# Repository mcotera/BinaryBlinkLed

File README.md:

# BinaryBlinkLed

# Program used
Eclipse CDT
KiCad
LibreOffice

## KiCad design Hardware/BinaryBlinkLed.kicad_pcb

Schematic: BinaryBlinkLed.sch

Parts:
BT1: 3V; JG_BAT
C1: 100nF; C_0805
D1: Led_01; Led_1206
D2, D3: Led_02; Led_1206
IC1: ATTINY13A-SS; so-8
P2: ISCP6; Pin_Header_Straight_2x03
Q1, Q2, Q3: BC848; SOT-23
R1, R2, R4, R6: 10K; r_0805
R3, R5, R7: 82R; r_0805
SW1: Switch_SPDT_x2; push_lock_6mm

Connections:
+BATT: C1.1, IC1.8 (VCC), P2.2, R1.2, R3.2, R5.2, R7.2, SW1.6
/LED02: IC1.2 (PB3(CLKI/ADC3/PCINT3)), R2.2
/LED03: IC1.3 (PB4(ADC2/PCINT4)), R4.2
/MISO: IC1.6 (PB1(MISO/AIN1/OC0B/INT0/PCINT1)), P2.1
/MOSI: IC1.5 (PB0(MOSI/AIN0/OC0A/PCINT0)), P2.4, R6.2
/RST: IC1.1 (PB5(~RESET~/ADC0/PCINT5/dW)), P2.5, R1.1
/SCK: IC1.7 (PB2(SCK/ADC1/T0/PCINT2)), P2.3
GND: BT1.2, C1.2, IC1.4 (GND), P2.6, Q1.2 (E), Q2.2 (E), Q3.2 (E)
unnamed: BT1.1, SW1.5
unnamed: D1.1 (K), Q1.3 (C)
unnamed: D1.2 (A), R3.1
unnamed: D2.1 (K), Q2.3 (C)
unnamed: D2.2 (A), R5.1
unnamed: D3.1 (K), Q3.3 (C)
unnamed: D3.2 (A), R7.1
unnamed: Q1.1 (B), R2.1
unnamed: Q2.1 (B), R4.1
unnamed: Q3.1 (B), R6.1

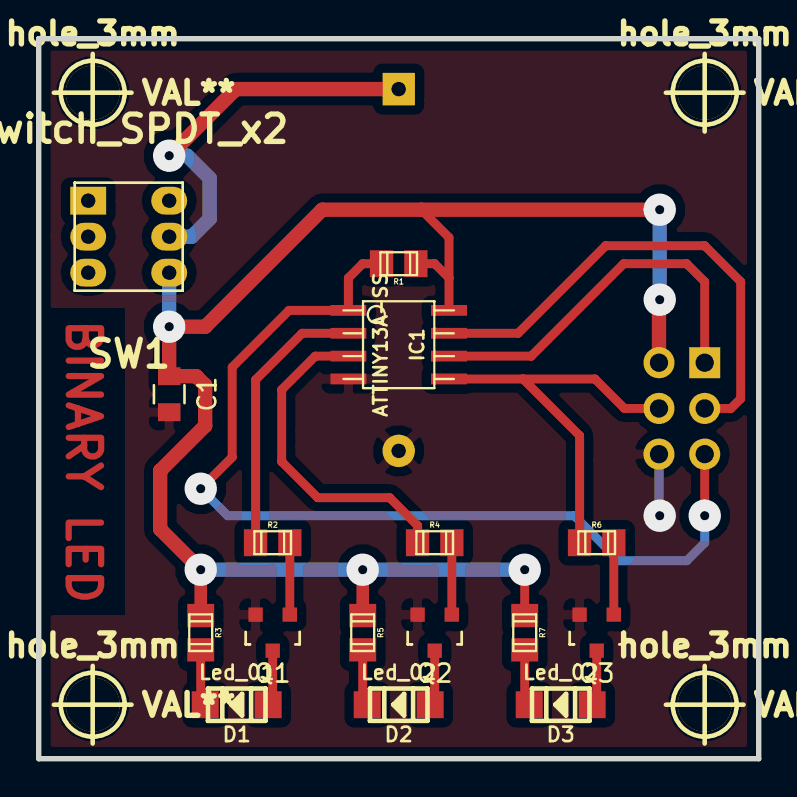
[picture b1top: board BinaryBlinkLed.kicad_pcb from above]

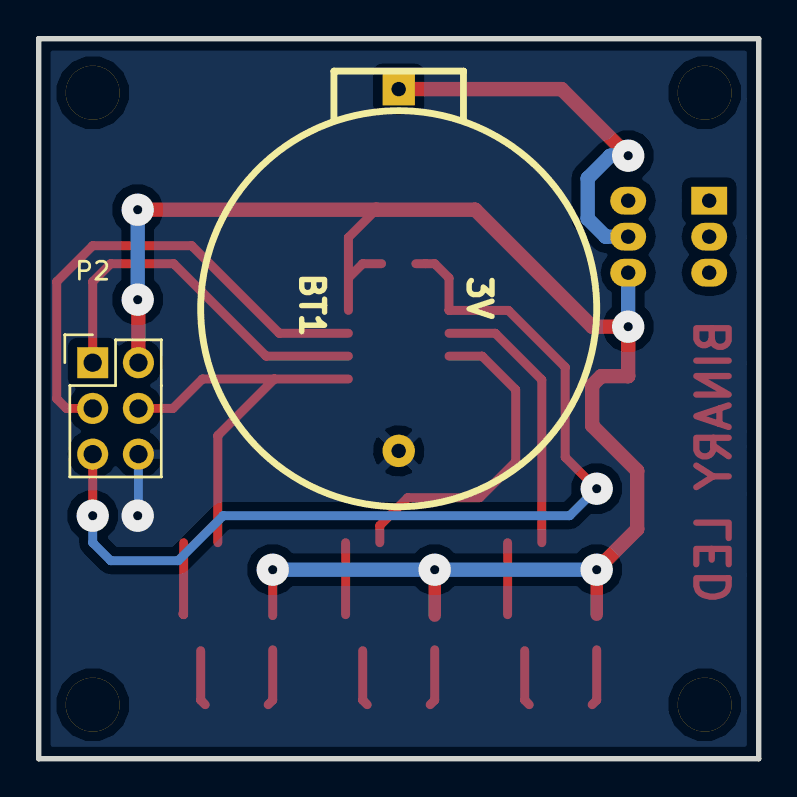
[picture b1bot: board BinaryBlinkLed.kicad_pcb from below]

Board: 2 copper layers, 40.0 x 40.0 mm, 22 parts (2 on the bottom side), 18 nets.

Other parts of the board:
hole_3mm, hole_3mm#2, hole_3mm#3, hole_3mm#4: VAL**; hole_3mm

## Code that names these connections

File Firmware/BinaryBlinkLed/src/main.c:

/*
 * main.c
 *
 *  Created on: Jun 19, 2017
 *      Author: mcotera
 */

#include <avr/io.h>
#include <util/delay.h>


#define	DDR_LED01	DDRB
#define	DDR_LED02	DDRB
#define	DDR_LED03	DDRB

#define	PORT_LED01	PORTB
#define	PORT_LED02	PORTB
#define	PORT_LED03	PORTB

#define	LED01		PB3
#define	LED02		PB4
#define	LED03		PB0

int main(void){

	// Set up Port B pin 3 and 4 mode to output
	DDR_LED01 |= (1 << LED01);
	DDR_LED02 |= (1 << LED02);
	DDR_LED03 |= (1 << LED03);

	for (;;) {
		// 0 binary
		PORT_LED01 &= ~(1 << LED01);
		PORT_LED02 &= ~(1 << LED02);
		PORT_LED03 &= ~(1 << LED03);
		_delay_ms(500);

		// 1 binary
		PORT_LED01 |= (1 << LED01);
		PORT_LED02 &= ~(1 << LED02);
		PORT_LED03 &= ~(1 << LED03);
		_delay_ms(500);

		// 2 binary
		PORT_LED01 &= ~(1 << LED01);
		PORT_LED02 |= (1 << LED02);
		PORT_LED03 &= ~(1 << LED03);
		_delay_ms(500);

		// 3 binary
		PORT_LED01 |= (1 << LED01);
		PORT_LED02 |= (1 << LED02);
		PORT_LED03 &= ~(1 << LED03);
		_delay_ms(500);

		// 4 binary
		PORT_LED01 &= ~(1 << LED01);
		PORT_LED02 &= ~(1 << LED02);
		PORT_LED03 |= (1 << LED03);
		_delay_ms(500);

		// 5 binary
		PORT_LED01 |= (1 << LED01);
		PORT_LED02 &= ~(1 << LED02);
		PORT_LED03 |= (1 << LED03);
		_delay_ms(500);

		// 6 binary
		PORT_LED01 &= ~(1 << LED01);
		PORT_LED02 |= (1 << LED02);
		PORT_LED03 |= (1 << LED03);
		_delay_ms(500);

		// 7 binary
		PORT_LED01 |= (1 << LED01);
		PORT_LED02 |= (1 << LED02);
		PORT_LED03 |= (1 << LED03);
		_delay_ms(500);

	}
	return 0;
}

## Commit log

2017-06-18 add proyect description
2017-06-18 add block diagram of proyect
2017-06-18 add EDA files, eschema with regulator 3.3V
2017-06-18 Correct value of resistor for supply voltaje 3.3V
2017-06-18 gitignore file added, this is eda file
2017-06-18 Updated .gitignore
    change *bak with .bak
2017-06-18 updated .gitignore
    change .bak with *.bak
2017-06-18 set value and name of some components
2017-06-18 Remove regulator, set value and name of some components
2017-06-19 select packages of components
2017-06-19 net file added
2017-06-20 ignore eWS folder added in gitignore
2017-06-20 Firmware part added, used attiny13a
2017-06-20 Firmware part added, used attiny13a, other method
2017-06-20 Flow diagram of firmware project added
2017-06-20 Create README.md
    Mention of software tools used
2017-09-04 update of schematic, change footprint of switch and battery
2017-09-04 library of JG and MC
2017-09-04 firmware system updated
2017-09-09 footprinft resistor changed, walter library used
2017-09-09 main.c updated
2017-09-09 BinaryBlinkLed.sch updated
